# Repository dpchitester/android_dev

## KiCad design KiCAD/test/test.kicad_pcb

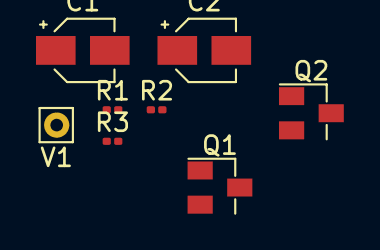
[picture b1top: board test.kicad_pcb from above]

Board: 2 copper layers, 8 parts (0 on the bottom side), 6 nets, no tracks yet.

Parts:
C1: 1nF; CP_Elec_3x5.3
C2: 3nF; CP_Elec_3x5.3
Q1, Q2: QNPN; SuperSOT-3
R1: 500; R_0201_0603Metric
R2: 1k; R_0201_0603Metric
R3: 1.2k; R_0201_0603Metric
V1: VSIN; Pin_D0.7mm_L6.5mm_W1.8mm_FlatFork

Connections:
unnamed: C1.1, Q1.1, Q2.2, R1.2
unnamed: C1.2, V1.1
unnamed: C2.1, Q1.3, R2.1
unnamed: C2.2, Q2.3, R3.1
VCC: Q2.1, R1.1
VEE: R2.2, R3.2

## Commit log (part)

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2023-05-04 pybak
